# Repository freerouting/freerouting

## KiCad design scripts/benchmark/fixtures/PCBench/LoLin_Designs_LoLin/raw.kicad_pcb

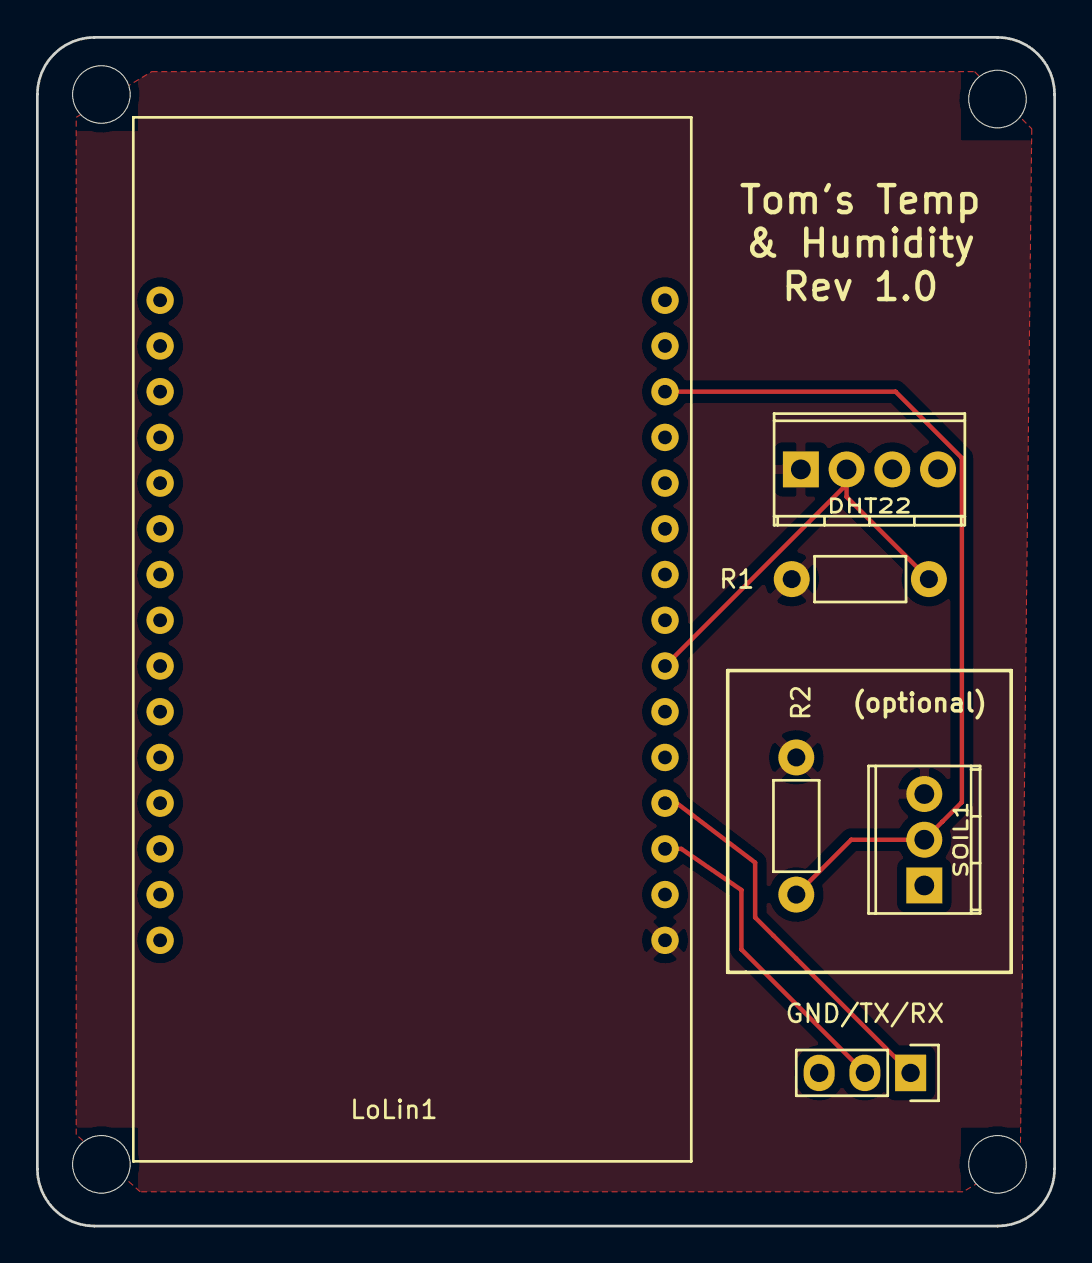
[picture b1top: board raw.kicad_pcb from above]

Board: 2 copper layers, 56.5 x 66.0 mm, 6 parts (0 on the bottom side), 6 nets.

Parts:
DHT22: DHT22; TerminalBlock_Pheonix_MPT-2.54mm_4pol
GND/TX/RX: RX/TX/GND; Pin_Header_Straight_1x03
LoLin1: LoLin_V3; LoLin
R1, R2: 4.7K; Resistor_Horizontal_RM7mm
SOIL1: SOIL; TerminalBlock_Pheonix_MPT-2.54mm_3pol

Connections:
3.3V: DHT22.1, LoLin1.16, R1.1, R2.2, SOIL1.3
GND: DHT22.4, GND/TX/RX.3, LoLin1.14, LoLin1.17, SOIL1.1
unnamed: GND/TX/RX.1, LoLin1.19
unnamed: GND/TX/RX.2, LoLin1.18
SOIL_TEMP: LoLin1.28, R2.1, SOIL1.2
TEMP_READING: DHT22.2, LoLin1.22, R1.2

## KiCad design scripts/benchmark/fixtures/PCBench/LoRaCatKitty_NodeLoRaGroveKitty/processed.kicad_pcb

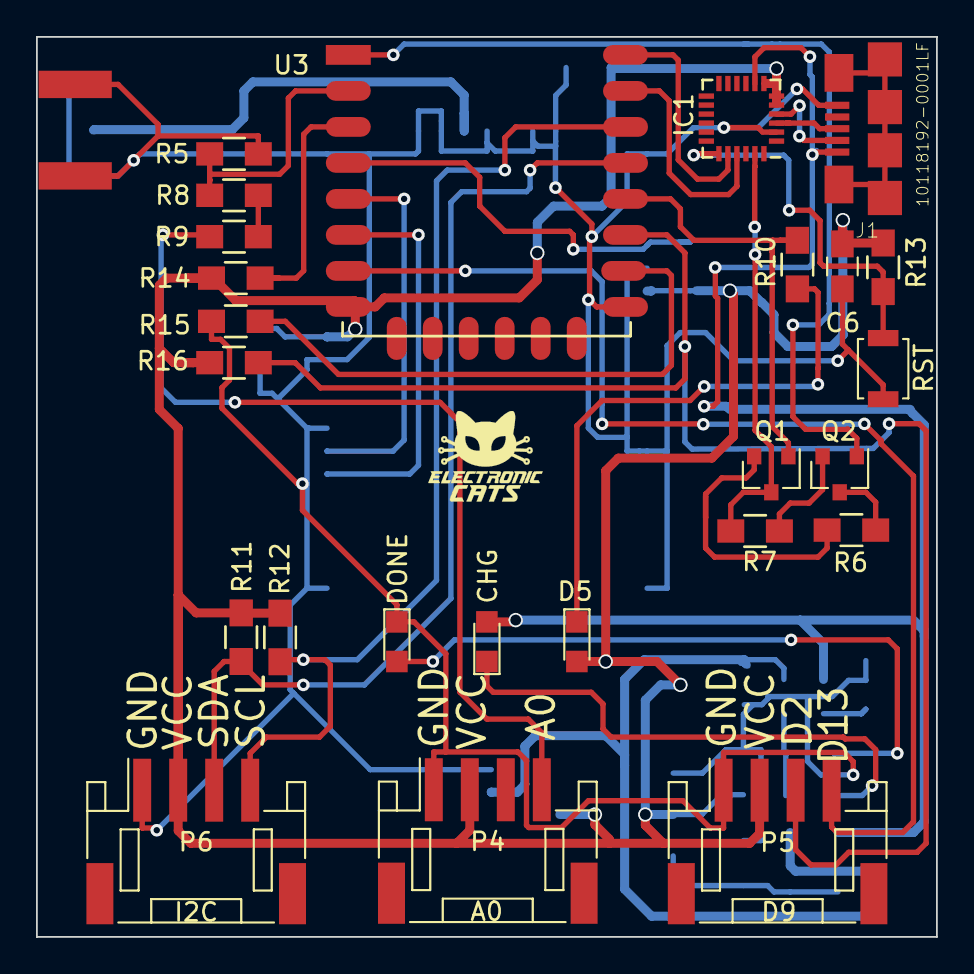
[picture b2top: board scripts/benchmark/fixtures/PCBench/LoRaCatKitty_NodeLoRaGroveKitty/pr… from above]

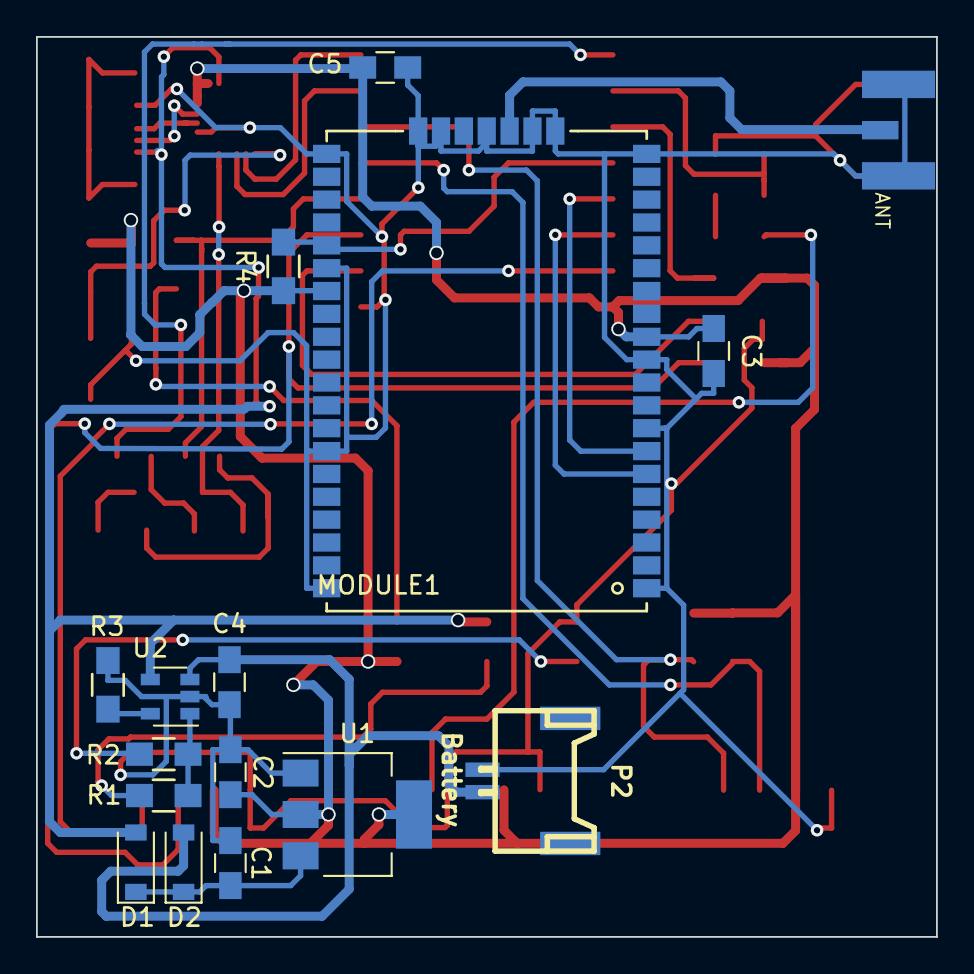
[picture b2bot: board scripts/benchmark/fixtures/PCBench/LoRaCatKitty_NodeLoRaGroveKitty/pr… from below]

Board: 2 copper layers, 50.0 x 50.0 mm, 41 parts (16 on the bottom side), 35 nets.

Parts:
A1: ANT; SMA_Conn_Ant
C1, C2: 4.7uF; C_0805_HandSoldering
C3, C5: 0.1uF; C_0805_HandSoldering
C4, C6: 10uF; C_0805_HandSoldering
D1, D2: MBR120; D_SOD-123
D3: CHG; LED_0805
D4: DONE; LED_0805
D5: Led; LED_0805
IC1: CP2104; QFN-24_4x4mm_Pitch0.5mm_NoMask
J1: 10118192-0001LF
MODULE1: RN2903; RN2483
P2: Battery; panelmate_smd_2
P4: A0; JST_PH_S4B-PH-SM4-TB_04x2.00mm_Angled
P5: D9; JST_PH_S4B-PH-SM4-TB_04x2.00mm_Angled
P6: I2C; JST_PH_S4B-PH-SM4-TB_04x2.00mm_Angled
Q1, Q2: MMBT2222A; SOT-23
R1, R2, R10: 330R; R_0805_HandSoldering
R3, R4, R6, R7, R13, R14, R15, R16: 10K; R_0805_HandSoldering
R5, R8, R9: 100K; R_0805_HandSoldering
R11, R12: 4.7K; R_0805_HandSoldering
RST: SW_RESET; SW_SPST_B3U-1000P
U1: AP2114; SOT-223-3Lead_TabPin2
U2: MCP73831T-2ATI/OT; SOT-23-5
U3: ESP8266-12E; ESP-12E

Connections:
+3V3: C2.1, C3.1, C5.1, C6.1, D5.2, IC1.5, IC1.6, IC1.7, MODULE1.12, MODULE1.34, P4.2, P5.2, P6.2, R4.1, R11.1, R12.1, R13.1, R14.1, R16.1, U1.2, U3.8
+BATT: C4.1, D2.2, P2.1, U2.3
/A0: P4.4, R9.1
/ADC: R5.1, R8.2, U3.2
/CH_PD: R14.2, U3.3
/DTR: IC1.23, Q1.3, R7.2
/GPIO0: Q1.1, R10.1, U3.12
/GPIO2: P5.3, R16.2, U3.11
/GPIO13: P5.4, U3.7
/GPIO15: R15.1, U3.10
/RESET: Q2.1, U3.1
/RST: IC1.19, R13.2, RST.2
/RST_RN: MODULE1.32, R4.2, U3.4
/RTS: Q2.3, R6.2
/RXD: IC1.21, U3.15
/SCL: P6.4, R12.2, U3.14
/SDA: P6.3, R11.2, U3.13
/SRX: MODULE1.6, U3.6
/STX: MODULE1.7, U3.5
/TXD: IC1.20, U3.16
GND: A1.2, A1.3, A1.4, A1.5, C1.2, C2.2, C3.2, C4.2, C5.2, C6.2, D4.1, IC1.2, J1.5, MODULE1.1, MODULE1.8, MODULE1.11, MODULE1.20, MODULE1.21, MODULE1.22, MODULE1.24, MODULE1.26, MODULE1.27, MODULE1.28, MODULE1.33, MODULE1.41, MODULE1.47, P2.2, P4.1, P5.1, P6.1, R3.2, R5.2, R15.2, RST.1, U1.1, U2.2, U3.9
unnamed: A1.1, MODULE1.23
unnamed: C1.1, D1.1, D2.1, U1.3
unnamed: D3.1, R1.2
unnamed: D4.2, R2.2
unnamed: D5.1, R10.2
unnamed: IC1.3, J1.3
unnamed: IC1.4, J1.2
unnamed: J1.M1, J1.M2, J1.S1, J1.S2, J1.S3, J1.S4
unnamed: Q1.2, R6.1
unnamed: Q2.2, R7.1
unnamed: R1.1, R2.1, U2.1
unnamed: R3.1, U2.5
unnamed: R8.1, R9.2
VCC: D1.2, D3.2, IC1.8, J1.1, U2.4

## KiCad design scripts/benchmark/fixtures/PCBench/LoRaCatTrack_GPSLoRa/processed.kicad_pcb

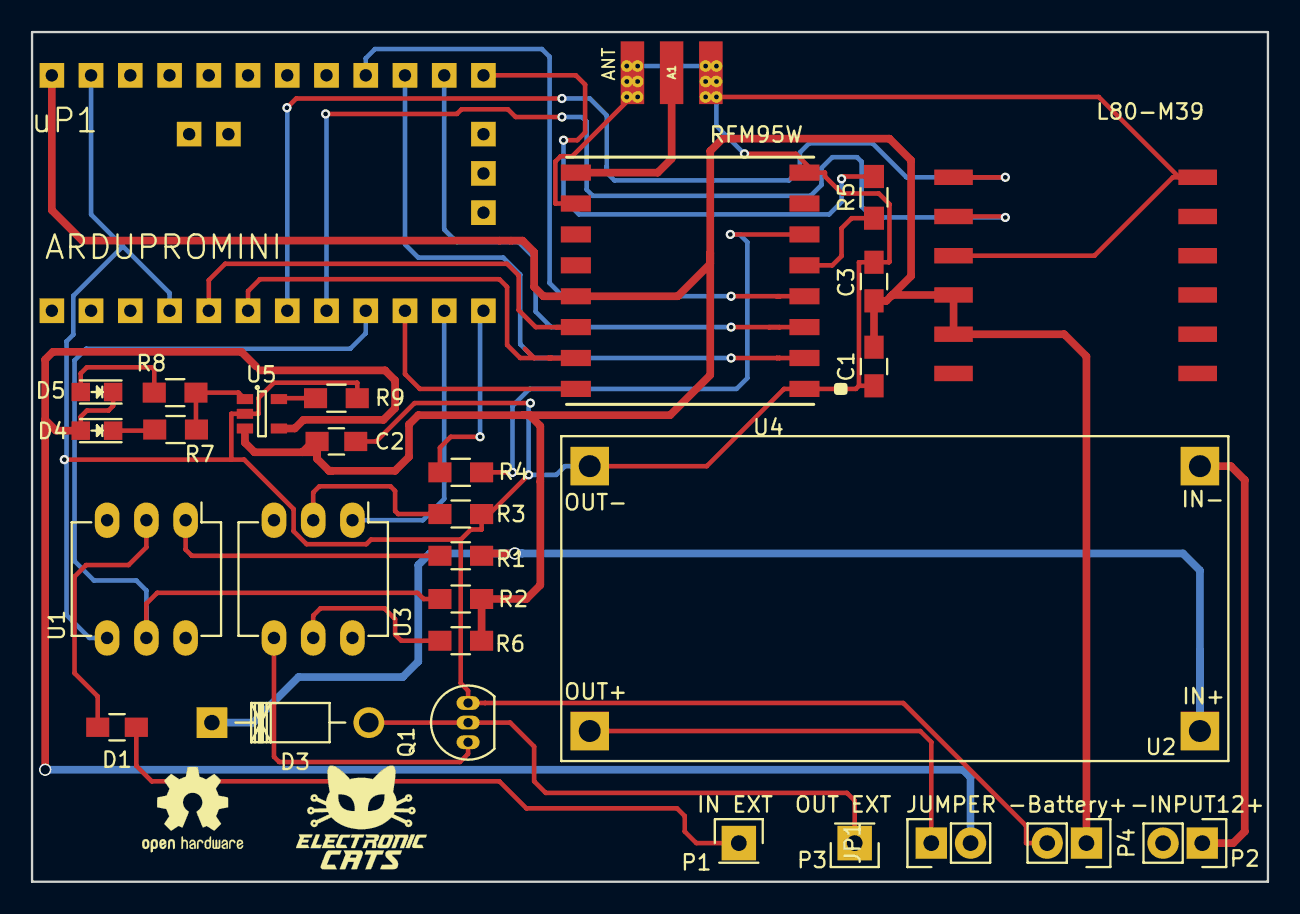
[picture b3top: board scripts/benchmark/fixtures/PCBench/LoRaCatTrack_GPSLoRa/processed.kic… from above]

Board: 2 copper layers, 80.0 x 55.0 mm, 30 parts (0 on the bottom side), 32 nets.

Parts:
A1: ANT; GSG-SMA-EDGE
C1, C3: 0.1uF; C_0805_HandSoldering
C2: 10uF; C_0805_HandSoldering
D1: D; C_0805_HandSoldering
D3: D; Diode_DO-41_SOD81_Horizontal_RM10
D4, D5: LED; LED_0805
JP1: JUMPER; Pin_Header_Straight_1x02
MODULE1: L80-M39; QUECTEL_L80-M39
P1: IN EXT; Pin_Header_Straight_1x01
P2: -INPUT12+; Pin_Header_Straight_1x02
P3: OUT EXT; Pin_Header_Straight_1x01
P4: -Battery+; Pin_Header_Straight_1x02
Q1: Q_NPN_BCE; TO-92_Inline_Narrow_Oval
R1, R6, R9: 1K; R_0805_HandSoldering
R2, R4, R5: 10K; R_0805_HandSoldering
R3, R7, R8: 220R; R_0805_HandSoldering
U1, U3: 4N26; DIP-6_W7.62mm_LongPads
U2: LM2596_Breakout; LM2596DC-DC
U4: RFM95W; XCVR_RFM95W-868S2
U5: MCP73831T-2ATI/OT; SOT-23-5
uP1: ARDUPROMINI; arduinoMiniPro2

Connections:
+5V: D4.2, D5.1, JP1.2, U5.4
+12C: D3.1, R1.1, U2.1
+BATT: C1.1, C2.1, C3.1, MODULE1.4, MODULE1.5, P4.1, R2.1, R6.1, U4.13, U5.3, uP1.19
/D6: R2.2, U1.5, uP1.15
/D8: U3.1, uP1.17
/DIO0: U4.14, uP1.11
/DIO1: U4.15, uP1.12
/DIO2: U4.16, uP1.16
/MISO: U4.2, uP1.28
/MOSI: U4.3, uP1.29
/NSS: R5.1, uP1.30
/RST: R4.1, uP1.18
/RX: MODULE1.2, uP1.14
/SCK: U4.4, uP1.27
/TX: MODULE1.1, uP1.13
GND: A1.2, A1.3, A1.4, A1.5, C1.2, C2.2, C3.2, MODULE1.3, MODULE1.12, P4.2, Q1.3, R3.2, R9.2, U1.4, U2.4, U4.1, U4.8, U4.10, U5.2, uP1.10, uP1.20
unnamed: A1.1, U4.9
unnamed: D1.1, P1.1
unnamed: D1.2, U1.2
unnamed: D3.2, P3.1, Q1.2
unnamed: D4.1, R7.2
unnamed: D5.2, R8.2
unnamed: JP1.1, U2.3
unnamed: P2.1, U2.2
unnamed: Q1.1, U3.4
unnamed: R1.2, U1.1
unnamed: R3.1, U3.2
unnamed: R4.2, U4.6
unnamed: R5.2, U4.5
unnamed: R6.2, U3.5
unnamed: R7.1, R8.1, U5.1
unnamed: R9.1, U5.5
